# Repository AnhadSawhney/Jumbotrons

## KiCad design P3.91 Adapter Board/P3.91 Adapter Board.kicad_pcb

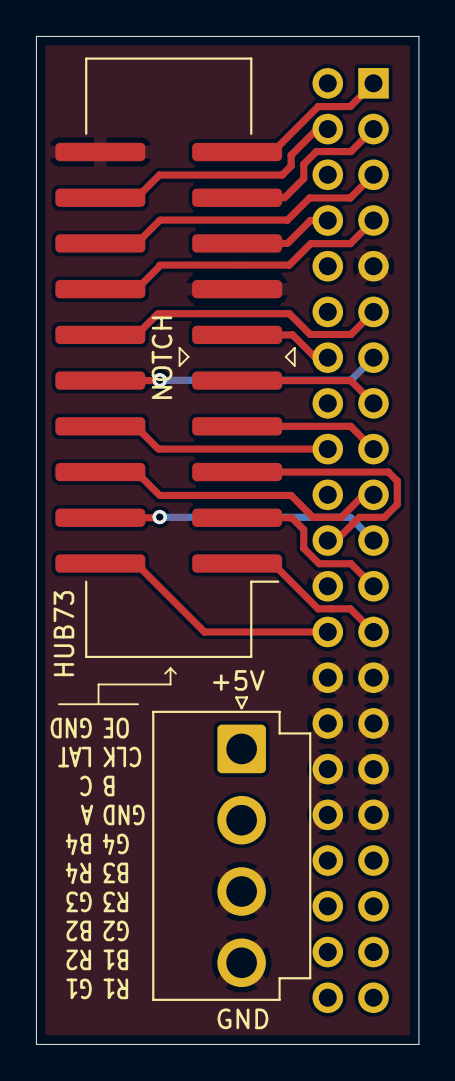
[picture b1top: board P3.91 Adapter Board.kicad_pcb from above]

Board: 2 copper layers, 21.2 x 56.0 mm, 3 parts (1 on the bottom side), 20 nets.

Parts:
J1: P3.91; PinHeader_2x21_P2.54mm_Vertical
J2: VH_4P; JST_VH_B4P-VH_1x04_P3.96mm_Vertical
J3: HUB73; IDC-Header_2x10_P2.54mm_Vertical_SMD

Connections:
+5V: J1.35, J1.36, J1.37, J1.38, J1.39, J1.40, J1.41, J1.42, J2.1, J2.2
/A: J1.7, J3.14
/B: J1.8, J3.15
/B1: J1.23, J3.3
/B2: J1.19, J3.6
/B3: J1.15, J3.9
/B4: J1.11, J3.12
/C: J1.5, J3.16
/CLK: J1.3, J3.17
/G1: J1.26, J3.2
/G2: J1.22, J3.5
/G3: J1.18, J3.8
/G4: J1.14, J3.11
/LAT: J1.4, J3.18
/OE: J1.1, J3.19
/R1: J1.25, J3.1
/R2: J1.21, J3.4
/R3: J1.17, J3.7
/R4: J1.13, J3.10
GND: J1.9, J1.24, J1.27, J1.28, J1.29, J1.30, J1.31, J1.32, J1.33, J1.34, J2.3, J2.4, J3.13, J3.20

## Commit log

2025-05-24 matrix cad files
2025-06-10 last panel design
2025-06-15 Design 3.91 and 8 panels
2025-06-15 finish p8 panel
2025-06-16 screws for p8 panel
2025-06-17 start p5 miguel panel
2025-06-19 miguel panel
2025-06-20 double wide p3.91 panel
2025-06-20 other panel
2025-06-23 start adding psu
2025-06-24 psu mount fix
2025-06-27 add driver cards
2025-07-01 adapter board
2025-07-01 board stuf
2025-07-02 start designing control card mount
2025-07-22 corner protectors and control board mount
2025-07-24 visualize
2025-08-05 mapping update
2025-10-13 stuff
